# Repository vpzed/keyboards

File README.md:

# Keyboards

Custom keyboards designed for fun.

- Toast - A blocky 34 key split ergo keyboard roughly based on the [A.dux](https://github.com/tapioki/cephalopoda/tree/main/Architeuthis%20dux) by tapioki.

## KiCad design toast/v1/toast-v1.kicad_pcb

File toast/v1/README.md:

# Toast v1

Config uses ergogen 3.1 fork at
https://github.com/MvEerd/ergogen
for the extra footprints

- PCB added
- Gerbers added
- Boards ordered from posted gerbers
- First keyboard build completed with no issues
- QMK a_dux firmware works with no changes

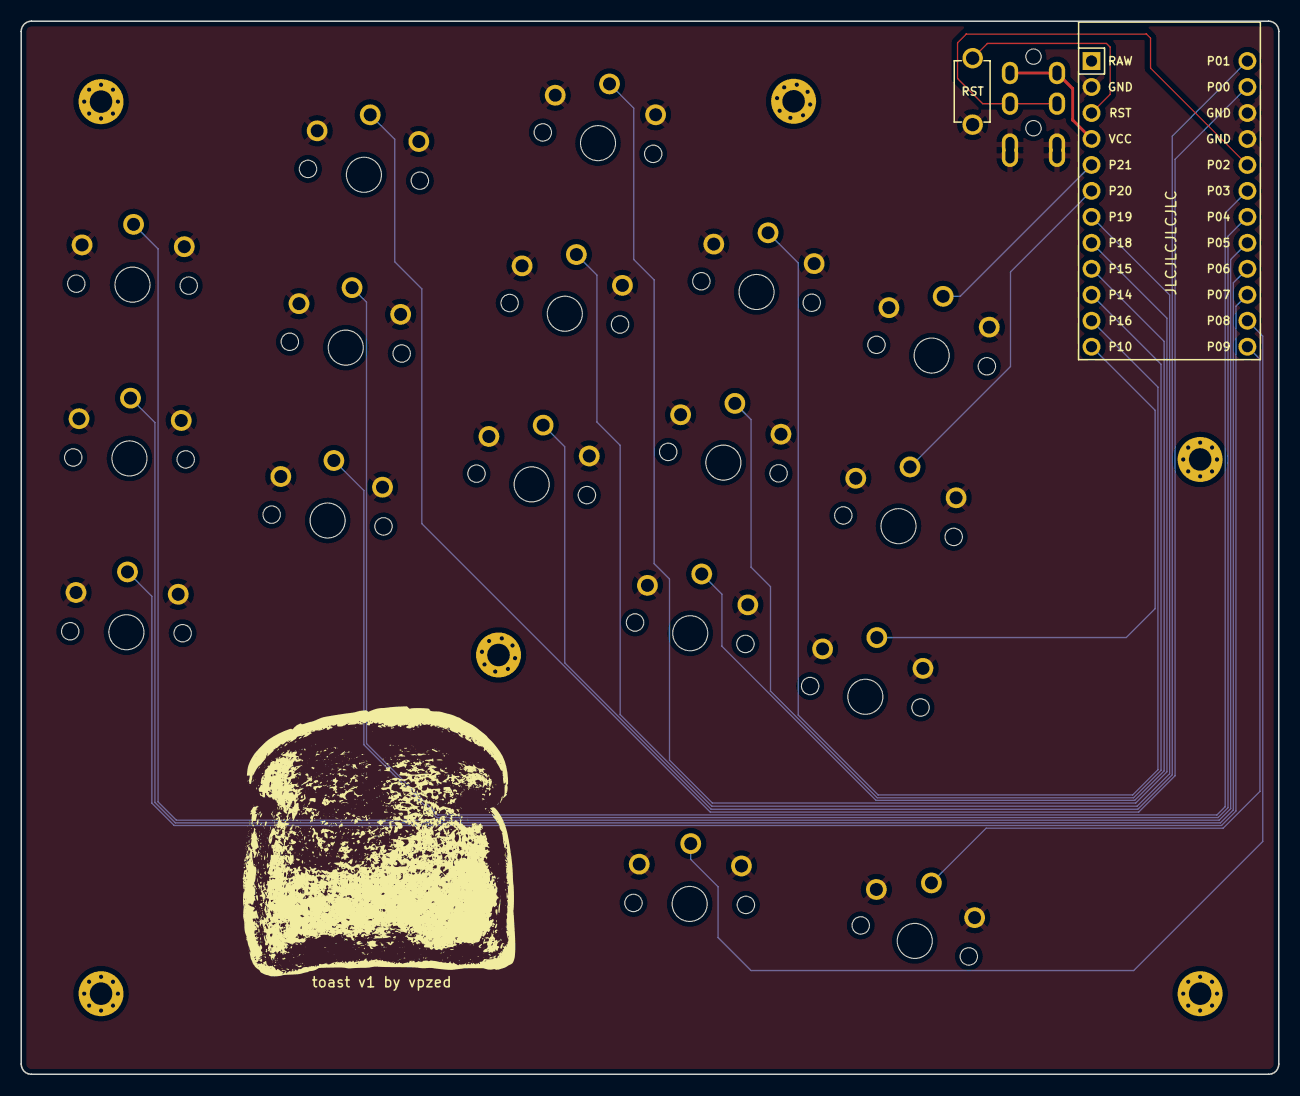
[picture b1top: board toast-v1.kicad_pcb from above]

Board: 2 copper layers, 123.0 x 103.0 mm, 25 parts (0 on the bottom side), 19 nets.

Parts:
B1: SW_RST; TACT_SWITCH_TVBP06
HOLE1, HOLE2, HOLE3, HOLE4, HOLE5, HOLE6: MountingHole_2.2mm_M2_Pad_Via
MCU1: ProMicro
S1, S2, S3, S4, S5, S6, S7, S8, S9, S10, S11, S12, S13, S14, S15, S16, S17: PG1350

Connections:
GND: B1.1, MCU1.2, MCU1.15, MCU1.16, S1.1, S2.1, S3.1, S4.1, S5.1, S6.1, S7.1, S8.1, S9.1, S10.1, S11.1, S12.1, S13.1, S14.1, S15.1, S16.1, S17.1
RST: B1.2, MCU1.3
fingers_index_bottom: MCU1.9, S10.2
fingers_index_home: MCU1.10, S11.2
fingers_index_top: MCU1.11, S12.2
fingers_inner_bottom: MCU1.12, S13.2
fingers_inner_home: MCU1.6, S14.2
fingers_inner_top: MCU1.5, S15.2
fingers_middle_bottom: MCU1.13, S7.2
fingers_middle_home: MCU1.7, S8.2
fingers_middle_top: MCU1.8, S9.2
fingers_pinky_bottom: MCU1.22, S1.2
fingers_pinky_home: MCU1.21, S2.2
fingers_pinky_top: MCU1.20, S3.2
fingers_ring_bottom: MCU1.19, S4.2
fingers_ring_home: MCU1.18, S5.2
fingers_ring_top: MCU1.14, S6.2
thumb_home: MCU1.24, S17.2
thumb_tucky: MCU1.23, S16.2

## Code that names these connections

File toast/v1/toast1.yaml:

# toast split ergo keyboard
# https://github.com/vpzed/keyboards/tree/main/toast/v1

# For ergogen v3.1
# https://github.com/ergogen/ergogen
# Thanks to all the helpful people at the Absolem Club Discord

### Begin

units:

  ### Reference units for components
  kx: 18			# choc switch x spacing of 18mm 
  ky: 17			# choc switch y spacing of 17mm
  cap_x: 17.5		# MBK keycap x size of 17.5mm
  cap_y: 16.5		# MBK keycap y size of 16.5mm
  plate_sq: 13.9	# plate hole to accomidate choc switch body of 13.80mm square
  # Reset switch footprint in Kicad is 3.5mm wide x 8.5mm long with pads vertical
  reset_x: 3.5
  reset_y: 8.5
  # PJ-320A footprint in Kicad is 6mm wide x 14mm long with connector facing up
  trrs_x: 6
  trrs_y: 14
  # ProMicro footprint in Kicad is 18mm wide x 33mm long with connector facing up
  mcu_x: 18
  mcu_y: 33
  # Ergogen web GUI weirdness
  visual_x: 1     # Visual representation of keycaps horizontal
  visual_y: 1     # Visual representation of keycaps vertical
  # Shift ergogen output into Kicad drawing frame
  frame_shift_x: 140
  frame_shift_y: -160

  ### Parameters for tweaking
  # Body angle is to provide a square edge on the pinky side to allow for tenting
  # while still supporting the desired angle of the columns for neutral wrist position
  body_angle: 11	# Angle in degrees from outer square edge on pinky side to middle column

  # Column stagger starting with pinky as reference, so 
  # positive going pinky through middle, then negative from middle to inner
  # pinky, ring, middle, index, inner
  ring_stag: ky * 2/3
  middle_stag: ky * 1/3
  index_stag: -ky * 2/3
  inner_stag: -ky * 1/6
  # adjustment to center ring column due to slop caused by pinky and ring splay
  ring_x_adj: 0
  
  # Pinky to ring column splay in degress
  pinky_splay: 5
  # Ring to middle column splay in degrees
  ring_splay: 5

points:

  zones.fingers:
    rotate: -body_angle + pinky_splay + ring_splay
    anchor:
      shift: [frame_shift_x, frame_shift_y]
    key: &key
      width: kx
      height: ky
      tags:
        keys: true 
      footprints:
        choc:
          type: choc
          nets:
            from: GND
            to: =name
          params:
              keycaps: true
              reverse: true
    columns:
      pinky:
        spread: kx
        origin: [0, -ky]
      ring:
        spread: kx
        stagger: ring_stag
        rotate: -pinky_splay
        origin: [0, -ky]
        key:
          shift: [ring_x_adj, 0]
      middle:
        spread: kx
        stagger: middle_stag
        rotate: -ring_splay
        origin: [0, -ky]
      index:
        spread: kx
        stagger: index_stag
        rotate: 0
        origin: [0, -ky]
      inner:
        spread: kx
        stagger: inner_stag
        origin: [0, -ky]
        rows: 
    rows:
      bottom.padding: ky
      home.padding: ky
      top.padding: ky

  zones.thumbs:
    anchor:
      ref: fingers_index_bottom
      shift: [5,-26]
    key: *key
    columns:
      first:
        key.name: thumb_tucky
        rotate: 10
      second:
        spread: kx
        rotate: -15
        origin: [-11, -ky]
        key:
          name: thumb_home
          shift: [0, 0.2]
    rows:
      only:
        padding: cy

  zones.mcu:
    anchor:
      ref: fingers_inner_top
      rotate: body_angle
      shift: [20, 19]
    key:
      name: mcu
      width: mcu_x
      height: mcu_y
      footprints:
      - type: promicro
        anchor:
          rotate: -90
        params:
          orientation: down
        nets:
          P7: fingers_pinky_bottom
          P6: fingers_pinky_home
          P5: fingers_pinky_top
          P4: fingers_ring_bottom
          P3: fingers_ring_home
          P0: fingers_ring_top
          P1: fingers_middle_bottom
          P19: fingers_middle_home
          P18: fingers_middle_top
          P15: fingers_index_bottom
          P14: fingers_index_home
          P16: fingers_index_top
          P10: fingers_inner_bottom
          P20: fingers_inner_home
          P21: fingers_inner_top
          P8: thumb_tucky
          P9: thumb_home

  zones.trrs:
    anchor:
      ref: mcu
      shift: [-(0.5*mcu_x + 0.5*trrs_x - 1), 16]
    key:
      name: trrs
      width: trrs_x
      height: trrs_y
      footprints:
      - type: trrs
        params:
          reverse: true
          symmetric: true
        nets:
          A: GND
          B: GND
          C: P2
          D: VCC

  zones.reset:
    anchor:
      ref: trrs
      shift: [-(0.5*trrs_x + 0.5*reset_x + 3.5), -5]
      rotate: 90
    key:
      name: reset
      width: reset_x
      height: reset_y
      footprints:
      - type: tactswitch
        nets:
          from: GND
          to: RST

outlines:
  exports:

    raw:
      - type: rectangle
        anchor:
          ref: fingers_inner_top
          rotate: body_angle
          shift: [-74, -86]
        size: [123, 103]
        corner: 0
        operation: stack 

    panel:
      - type: outline
        name: raw
        fillet: 1

pcbs:
  toast-v1:
    outlines:
      main:
        outline: panel
    footprints:
      # Above pinky column
      mounthole1:
        type: mountinghole
        anchor:
          ref: mcu
          #rotate: body_angle
          shift: [-104.5, 10]
        nets:
          from: GND
      # Below pinky column
      mounthole2:
        type: mountinghole
        anchor:
          ref: mcu
          #rotate: body_angle
          shift: [-104.5, -77.25]
        nets:
          from: GND
      # Below middle column
      mounthole3:
        type: mountinghole
        anchor:
          ref: fingers_middle_bottom
          shift: [0, -ky]
        nets:
          from: GND
      # Above index column
      mounthole4:
        type: mountinghole
        anchor:
          ref: fingers_index_top
          shift: [0, 19]
        nets:
          from: GND
      # Immediately below MCU
      mounthole5:
        type: mountinghole
        anchor:
          ref: mcu
          shift: [3, -25 ]
        nets:
          from: GND
      # Farther below MCU
      mounthole6:
        type: mountinghole
        anchor:
          ref: mcu
          shift: [3, -77.25]
        nets:
          from: GND


### End

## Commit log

2022-04-04 update readmes
2022-04-04 add toast prototype image
2022-04-04 update v1 readme
2022-04-06 added mounting holes and reset switch option
2022-04-06 corrected pcb name
2022-04-07 add pcb and update readme
2022-04-07 fix image links
2022-04-08 finals for order
2022-04-30 Update main Readme
2022-04-30 Update Readme with first board completed info
2022-04-30 Add photo of completed keyboard
2022-04-30 Update Readme with first build info and photo
2022-04-30 Added link to gerbers.zip
